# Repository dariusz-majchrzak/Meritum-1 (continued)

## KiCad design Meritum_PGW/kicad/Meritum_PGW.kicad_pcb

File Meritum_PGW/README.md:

# Meritum 1 - mainboard

This part of the project is the clone of the Meritum 1 mainboard.

## Files
This directory contains: 

* [BOM](bom) - Interactive HTML BOM
* [Gerber](gerber) - files (JLCPCB-compatible zip files)
* [IMG](img) - photos of the mainboard
* [KiCAD](kicad) - project design in KiCAD 10
* [Schematic](schematic) - Schematic in PDF format

## Assembling
WIP.

More to follow.

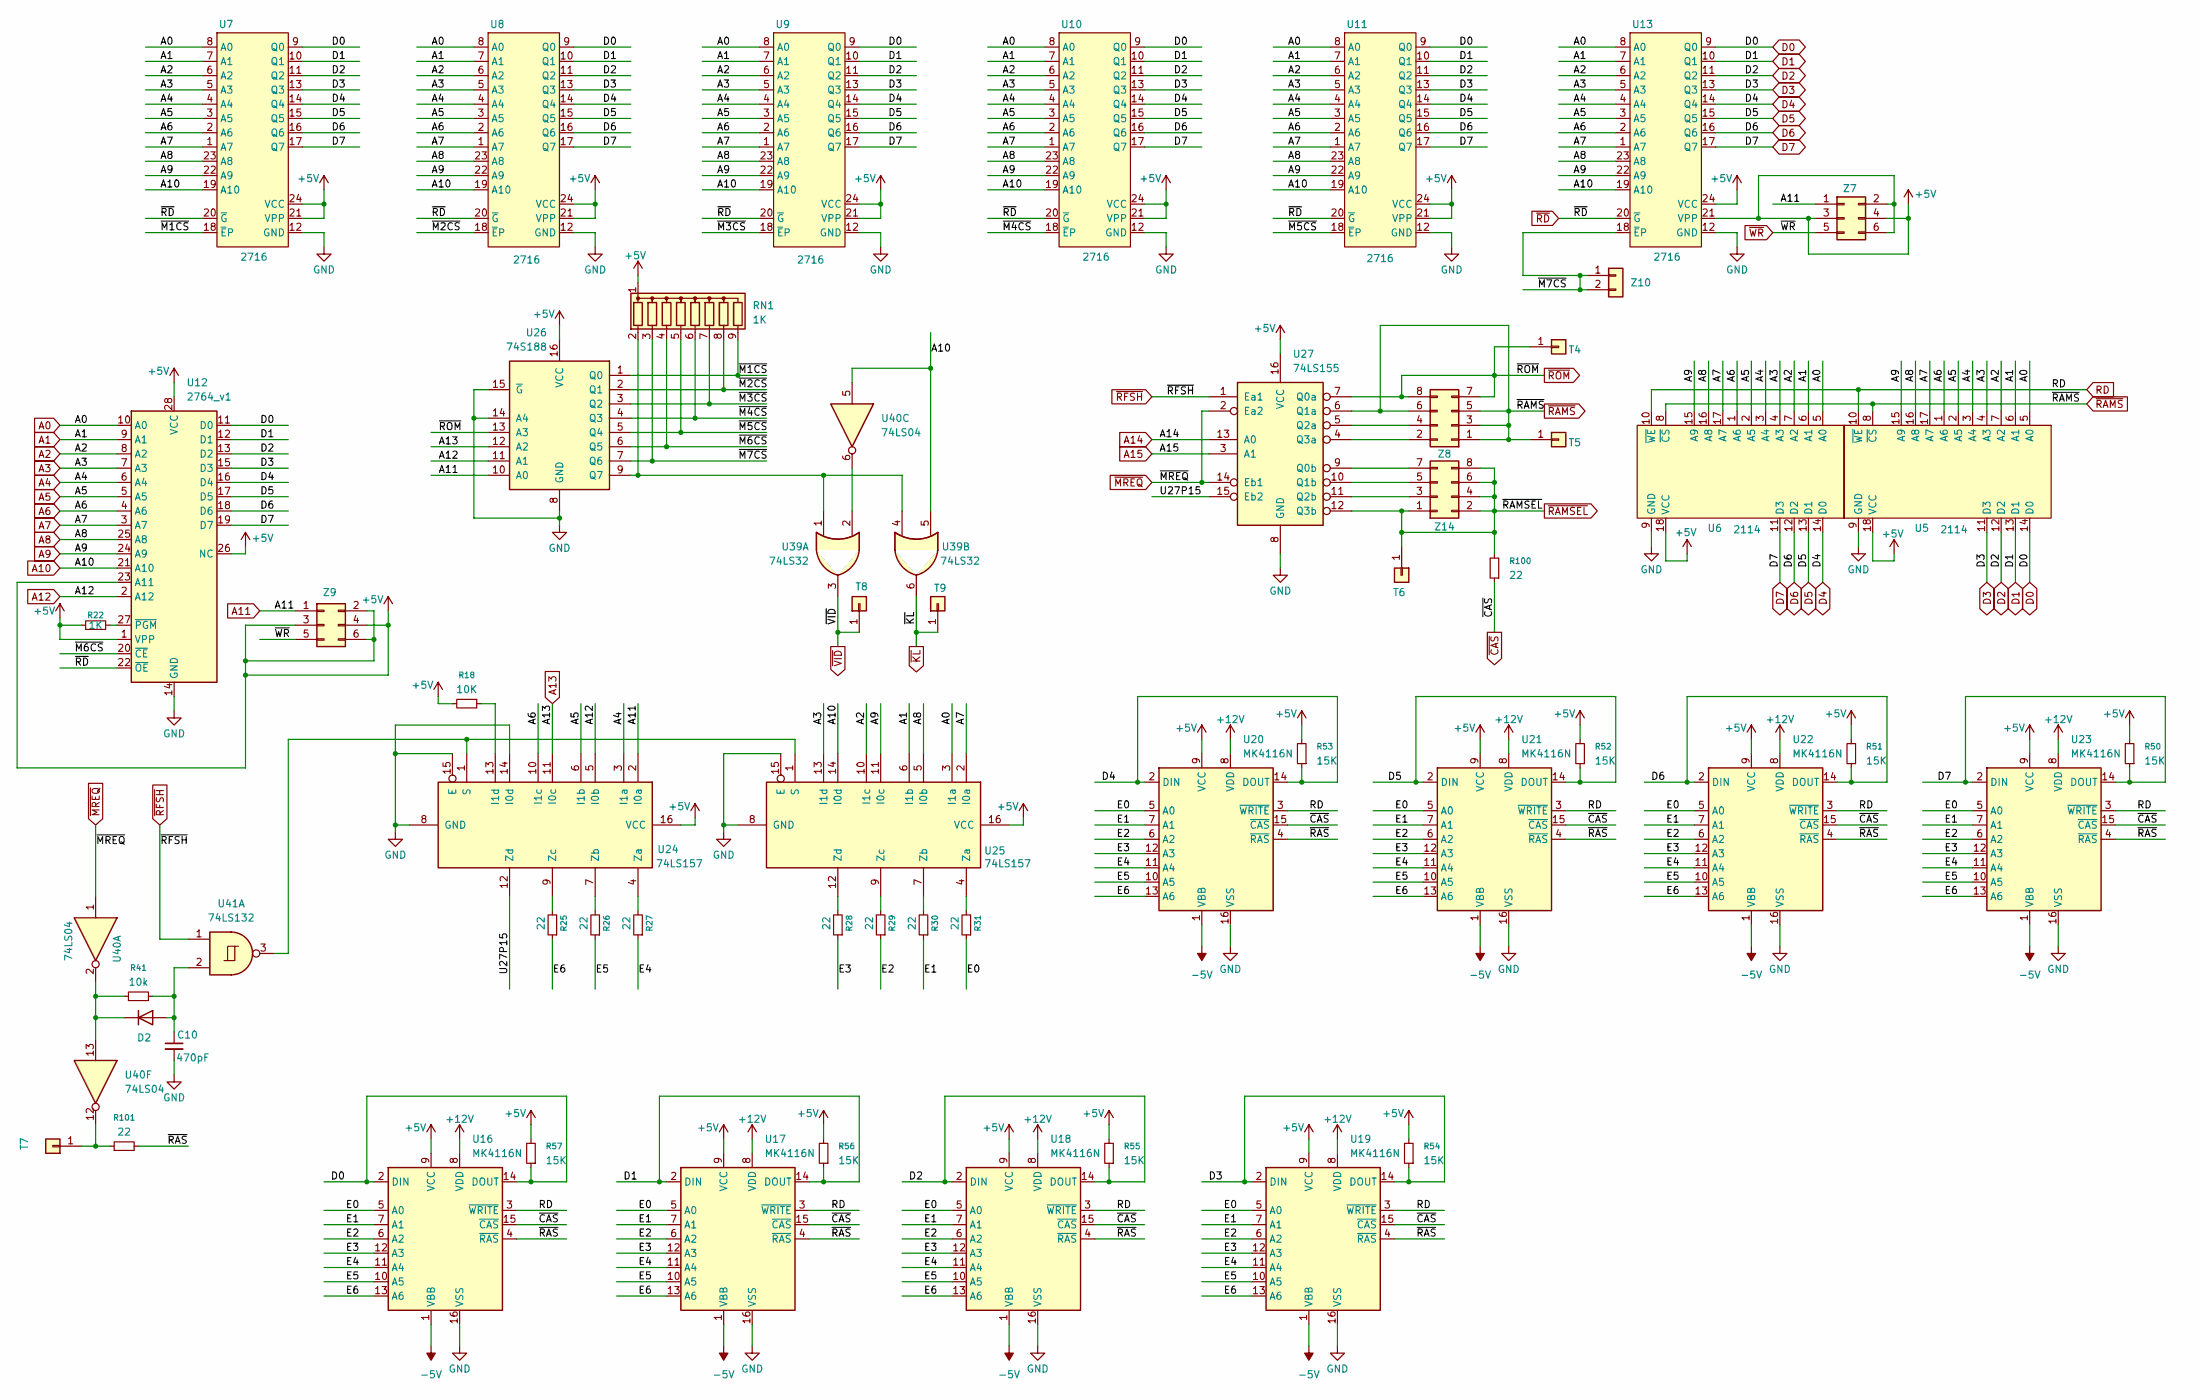
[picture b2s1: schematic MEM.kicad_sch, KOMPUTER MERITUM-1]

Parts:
C10: 470pF; c_100
D2: 1N4148; D_DO-35_SOD27_P10.16mm_Horizontal
R18: 10K; r_400
R22: 1K; R_Axial_DIN0207_L6.3mm_D2.5mm_P2.54mm_Vertical
R25, R26, R27, R28, R29, R30, R31, R100, R101: 22; r_400
R41: 10k; r_400
R50, R51, R52, R53, R54, R55, R56, R57: 15K; R_Axial_DIN0207_L6.3mm_D2.5mm_P2.54mm_Vertical
RN1: 1K; R_Array_SIP9
T4, T5, T6, T7, T8, T9: T18; pin
U5, U6: 2114; DIP-18_W7.62mm_Socket_LongPads
U7, U8, U9, U10, U11, U13: 2716; DIP-24_W15.24mm_LongPads
U12: 2764_v1; DIP-28_W15.24mm_LongPads
U16, U17, U18, U19, U20, U21, U22, U23: MK4116N; DIP-16_W7.62mm_LongPads
U24, U25: 74LS157; DIP-16_W7.62mm_LongPads
U26: 74S188; DIP-16_W7.62mm_LongPads
U27: 74LS155; DIP-16_W7.62mm_LongPads
U39: 74LS32; DIP-14_W7.62mm_LongPads
U40: 74LS04; DIP-14_W7.62mm_LongPads
U41: 74LS132; DIP-14_W7.62mm_LongPads
Z7: Z3; PinHeader_2x03_P2.54mm_Vertical
Z8, Z14: Conn_02x04_Odd_Even; PinHeader_2x04_P2.54mm_Vertical
Z9: Z4; PinHeader_2x03_P2.54mm_Vertical
Z10: Conn_01x02; PinHeader_1x02_P2.54mm_Vertical

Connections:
+5V: R18.2, R22.1, R50.2, R51.2, R52.2, R53.2, R54.2, R55.2, R56.2, R57.2, RN1.1 (common), U5.18 (VCC), U6.18 (VCC), U7.21 (VPP), U7.24 (VCC), U8.21 (VPP), U8.24 (VCC), U9.21 (VPP), U9.24 (VCC), U10.21 (VPP), U10.24 (VCC), U11.21 (VPP), U11.24 (VCC), U12.1 (VPP), U12.23 (A11), U12.26 (NC), U12.28 (VCC), U13.21 (VPP), U13.24 (VCC), U16.9 (VCC), U17.9 (VCC), U18.9 (VCC), U19.9 (VCC), U20.9 (VCC), U21.9 (VCC), U22.9 (VCC), U23.9 (VCC), U24.16 (VCC), U25.16 (VCC), U26.16 (VCC), U27.16 (VCC), Z7.2, Z7.3, Z7.4, Z7.6, Z9.2, Z9.3, Z9.4, Z9.6; also elsewhere on the board
+12V: U16.8 (VDD), U17.8 (VDD), U18.8 (VDD), U19.8 (VDD), U20.8 (VDD), U21.8 (VDD), U22.8 (VDD), U23.8 (VDD); also elsewhere on the board
-5V: U16.1 (VBB), U17.1 (VBB), U18.1 (VBB), U19.1 (VBB), U20.1 (VBB), U21.1 (VBB), U22.1 (VBB), U23.1 (VBB); also elsewhere on the board
/MEM/E0: R31.1, U16.5 (A0), U17.5 (A0), U18.5 (A0), U19.5 (A0), U20.5 (A0), U21.5 (A0), U22.5 (A0), U23.5 (A0)
/MEM/E1: R30.1, U16.7 (A1), U17.7 (A1), U18.7 (A1), U19.7 (A1), U20.7 (A1), U21.7 (A1), U22.7 (A1), U23.7 (A1)
/MEM/E2: R29.1, U16.6 (A2), U17.6 (A2), U18.6 (A2), U19.6 (A2), U20.6 (A2), U21.6 (A2), U22.6 (A2), U23.6 (A2)
/MEM/E3: R28.1, U16.12 (A3), U17.12 (A3), U18.12 (A3), U19.12 (A3), U20.12 (A3), U21.12 (A3), U22.12 (A3), U23.12 (A3)
/MEM/E4: R27.1, U16.11 (A4), U17.11 (A4), U18.11 (A4), U19.11 (A4), U20.11 (A4), U21.11 (A4), U22.11 (A4), U23.11 (A4)
/MEM/E5: R26.1, U16.10 (A5), U17.10 (A5), U18.10 (A5), U19.10 (A5), U20.10 (A5), U21.10 (A5), U22.10 (A5), U23.10 (A5)
/MEM/E6: R25.1, U16.13 (A6), U17.13 (A6), U18.13 (A6), U19.13 (A6), U20.13 (A6), U21.13 (A6), U22.13 (A6), U23.13 (A6)
/MEM/U27P15: U24.12 (Zd), U27.15 (Eb2)
/MEM/~M1CS: RN1.9 (R8), U7.18 (~EP), U26.1 (Q0)
/MEM/~M2CS: RN1.8 (R7), U8.18 (~EP), U26.2 (Q1)
/MEM/~M3CS: RN1.7 (R6), U9.18 (~EP), U26.3 (Q2)
/MEM/~M4CS: RN1.6 (R5), U10.18 (~EP), U26.4 (Q3)
/MEM/~M5CS: RN1.5 (R4), U11.18 (~EP), U26.5 (Q4)
/MEM/~M6CS: RN1.4 (R3), U12.20 (~CE), U26.6 (Q5)
/MEM/~M7CS: RN1.3 (R2), U13.18 (~EP), U26.7 (Q6), Z10.1, Z10.2
/MEM/~RAS: R101.2, U16.4 (~RAS), U17.4 (~RAS), U18.4 (~RAS), U19.4 (~RAS), U20.4 (~RAS), U21.4 (~RAS), U22.4 (~RAS), U23.4 (~RAS)
A0: U5.5 (A0), U6.5 (A0), U7.8 (A0), U8.8 (A0), U9.8 (A0), U10.8 (A0), U11.8 (A0), U12.10 (A0), U13.8 (A0), U25.3 (I1a); also elsewhere on the board
A1: U5.6 (A1), U6.6 (A1), U7.7 (A1), U8.7 (A1), U9.7 (A1), U10.7 (A1), U11.7 (A1), U12.9 (A1), U13.7 (A1), U25.6 (I1b); also elsewhere on the board
A2: U5.7 (A2), U6.7 (A2), U7.6 (A2), U8.6 (A2), U9.6 (A2), U10.6 (A2), U11.6 (A2), U12.8 (A2), U13.6 (A2), U25.10 (I1c); also elsewhere on the board
A3: U5.4 (A3), U6.4 (A3), U7.5 (A3), U8.5 (A3), U9.5 (A3), U10.5 (A3), U11.5 (A3), U12.7 (A3), U13.5 (A3), U25.13 (I1d); also elsewhere on the board
A4: U5.3 (A4), U6.3 (A4), U7.4 (A4), U8.4 (A4), U9.4 (A4), U10.4 (A4), U11.4 (A4), U12.6 (A4), U13.4 (A4), U24.3 (I1a); also elsewhere on the board
A5: U5.2 (A5), U6.2 (A5), U7.3 (A5), U8.3 (A5), U9.3 (A5), U10.3 (A5), U11.3 (A5), U12.5 (A5), U13.3 (A5), U24.6 (I1b); also elsewhere on the board
A6: U5.1 (A6), U6.1 (A6), U7.2 (A6), U8.2 (A6), U9.2 (A6), U10.2 (A6), U11.2 (A6), U12.4 (A6), U13.2 (A6), U24.10 (I1c); also elsewhere on the board
A7: U5.17 (A7), U6.17 (A7), U7.1 (A7), U8.1 (A7), U9.1 (A7), U10.1 (A7), U11.1 (A7), U12.3 (A7), U13.1 (A7), U25.2 (I0a); also elsewhere on the board
A8: U5.16 (A8), U6.16 (A8), U7.23 (A8), U8.23 (A8), U9.23 (A8), U10.23 (A8), U11.23 (A8), U12.25 (A8), U13.23 (A8), U25.5 (I0b); also elsewhere on the board
A9: U5.15 (A9), U6.15 (A9), U7.22 (A9), U8.22 (A9), U9.22 (A9), U10.22 (A9), U11.22 (A9), U12.24 (A9), U13.22 (A9), U25.11 (I0c); also elsewhere on the board
A10: U7.19 (A10), U8.19 (A10), U9.19 (A10), U10.19 (A10), U11.19 (A10), U12.21 (A10), U13.19 (A10), U25.14 (I0d), U39.5, U40.5; also elsewhere on the board
A11: U24.2 (I0a), U26.10 (A0), Z7.1, Z9.1; also elsewhere on the board
A12: U12.2 (A12), U24.5 (I0b), U26.11 (A1); also elsewhere on the board
A13: U24.11 (I0c), U26.12 (A2); also elsewhere on the board
A14: U27.13 (A0); also elsewhere on the board
A15: U27.3 (A1); also elsewhere on the board
BD0: R57.1, U5.14 (D0), U7.9 (Q0), U8.9 (Q0), U9.9 (Q0), U10.9 (Q0), U11.9 (Q0), U12.11 (D0), U13.9 (Q0), U16.2 (DIN), U16.14 (DOUT); also elsewhere on the board
D1: R56.1, U5.13 (D1), U7.10 (Q1), U8.10 (Q1), U9.10 (Q1), U10.10 (Q1), U11.10 (Q1), U12.12 (D1), U13.10 (Q1), U17.2 (DIN), U17.14 (DOUT); also elsewhere on the board
D2: R55.1, U5.12 (D2), U7.11 (Q2), U8.11 (Q2), U9.11 (Q2), U10.11 (Q2), U11.11 (Q2), U12.13 (D2), U13.11 (Q2), U18.2 (DIN), U18.14 (DOUT); also elsewhere on the board
D3: R54.1, U5.11 (D3), U7.13 (Q3), U8.13 (Q3), U9.13 (Q3), U10.13 (Q3), U11.13 (Q3), U12.15 (D3), U13.13 (Q3), U19.2 (DIN), U19.14 (DOUT); also elsewhere on the board
D4: R53.1, U6.14 (D0), U7.14 (Q4), U8.14 (Q4), U9.14 (Q4), U10.14 (Q4), U11.14 (Q4), U12.16 (D4), U13.14 (Q4), U20.2 (DIN), U20.14 (DOUT); also elsewhere on the board
D5: R52.1, U6.13 (D1), U7.15 (Q5), U8.15 (Q5), U9.15 (Q5), U10.15 (Q5), U11.15 (Q5), U12.17 (D5), U13.15 (Q5), U21.2 (DIN), U21.14 (DOUT); also elsewhere on the board
D6: R51.1, U6.12 (D2), U7.16 (Q6), U8.16 (Q6), U9.16 (Q6), U10.16 (Q6), U11.16 (Q6), U12.18 (D6), U13.16 (Q6), U22.2 (DIN), U22.14 (DOUT); also elsewhere on the board
D7: R50.1, U6.11 (D3), U7.17 (Q7), U8.17 (Q7), U9.17 (Q7), U10.17 (Q7), U11.17 (Q7), U12.19 (D7), U13.17 (Q7), U23.2 (DIN), U23.14 (DOUT); also elsewhere on the board
GND: C10.2, U5.9 (GND), U6.9 (GND), U7.12 (GND), U8.12 (GND), U9.12 (GND), U10.12 (GND), U11.12 (GND), U12.14 (GND), U13.12 (GND), U16.16 (VSS), U17.16 (VSS), U18.16 (VSS), U19.16 (VSS), U20.16 (VSS), U21.16 (VSS), U22.16 (VSS), U23.16 (VSS), U24.8 (GND), U24.14 (I0d), U24.15 (E), U25.8 (GND), U25.15 (E), U26.8 (GND), U26.14 (A4), U26.15 (~G), U27.8 (GND); also elsewhere on the board
unnamed: C10.1, D2.2 (A), R41.2, U41.2
unnamed: D2.1 (K), R41.1, U40.2, U40.13
unnamed: RN1.2 (R1), U26.9 (Q7), U39.1, U39.4
unnamed: R101.1, T7.1 (Pin_1_1), U40.12
unnamed: R22.2, U12.27 (~PGM)
unnamed: R18.1, U24.13 (I1d)
unnamed: U24.1 (S), U25.1 (S), U41.3
unnamed: R27.2, U24.4 (Za)
unnamed: R26.2, U24.7 (Zb)
unnamed: R25.2, U24.9 (Zc)
unnamed: R31.2, U25.4 (Za)
unnamed: R30.2, U25.7 (Zb)
unnamed: R29.2, U25.9 (Zc)
unnamed: R28.2, U25.12 (Zd)
unnamed: U27.9 (Q0b), Z14.7
unnamed: U27.10 (Q1b), Z14.5
unnamed: U27.5 (Q2a), Z8.4
unnamed: U27.11 (Q2b), Z14.3
unnamed: U27.4 (Q3a), Z8.2
unnamed: U39.2, U40.6
RD: U5.10 (~WE), U6.10 (~WE), U16.3 (~WRITE), U17.3 (~WRITE), U18.3 (~WRITE), U19.3 (~WRITE), U20.3 (~WRITE), U21.3 (~WRITE), U22.3 (~WRITE), U23.3 (~WRITE); also elsewhere on the board
~CAS: R100.1, U16.15 (~CAS), U17.15 (~CAS), U18.15 (~CAS), U19.15 (~CAS), U20.15 (~CAS), U21.15 (~CAS), U22.15 (~CAS), U23.15 (~CAS)
~KL: T9.1 (Pin_1_1), U39.6; also elsewhere on the board
~MREQ: U27.2 (Ea2), U27.14 (Eb1), U40.1; also elsewhere on the board
~RAMSEL: R100.2, T6.1 (Pin_1_1), U27.12 (Q3b), Z14.1, Z14.2, Z14.4, Z14.6, Z14.8; also elsewhere on the board
~RAMS: T5.1 (Pin_1_1), U5.8 (~CS), U6.8 (~CS), U27.6 (Q1a), Z8.1, Z8.3, Z8.5, Z8.6; also elsewhere on the board
~RD: U7.20 (~G), U8.20 (~G), U9.20 (~G), U10.20 (~G), U11.20 (~G), U12.22 (~OE), U13.20 (~G); also elsewhere on the board
~RFSH: U27.1 (Ea1), U41.1; also elsewhere on the board
~ROM: T4.1 (Pin_1_1), U26.13 (A3), U27.7 (Q0a), Z8.7, Z8.8; also elsewhere on the board
~VID: T8.1 (Pin_1_1), U39.3; also elsewhere on the board
~WR: Z7.5, Z9.5; also elsewhere on the board

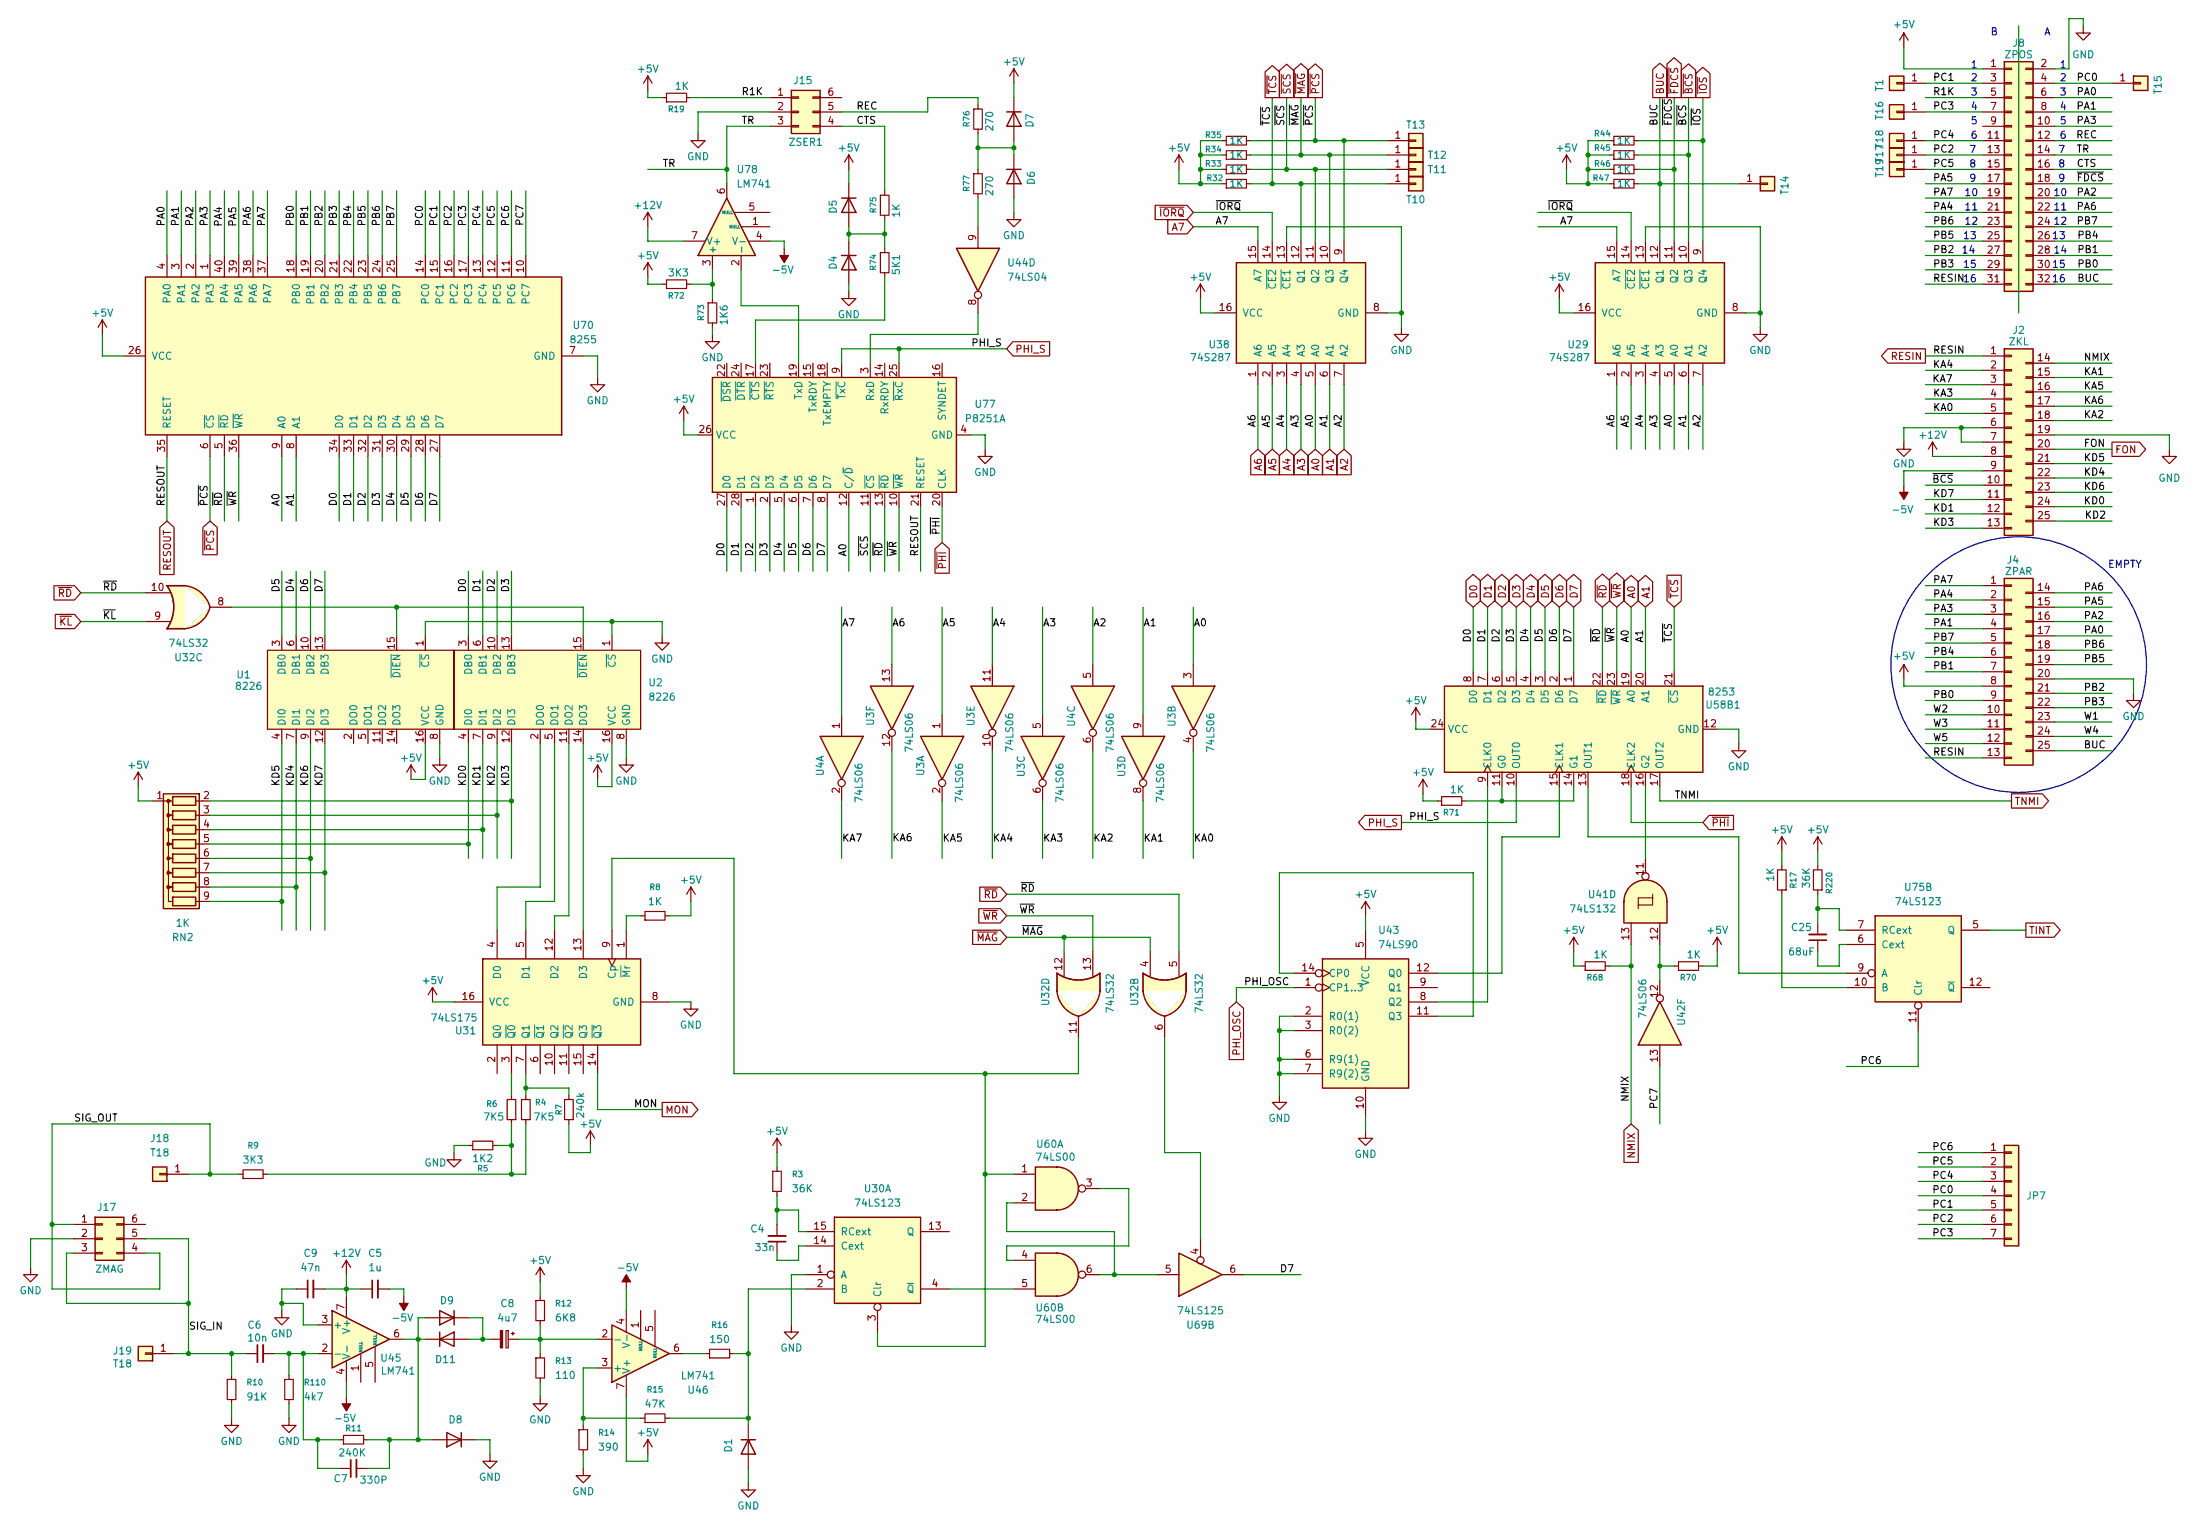
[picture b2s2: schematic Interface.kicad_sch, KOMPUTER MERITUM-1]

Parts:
C4: 33n; c_200
C5: 1u; c_200
C6: 10n; C_Rect_L4.0mm_W2.5mm_P2.50mm
C7: 330P; c_100
C8: 4u7; c_200
C9: 47n; c_200
C25: 68uF; CP_Radial_D5.0mm_P2.50mm
D1: 1N4148; D_DO-35_SOD27_P10.16mm_Horizontal
D4, D5: 1N4148WT; D_DO-35_SOD27_P2.54mm_Vertical_KathodeUp
D6, D7: 1N4148WT; D_DO-35_SOD27_P10.16mm_Horizontal
D8, D9, D11: 1N4148; D_DO-35_SOD27_P5.08mm_Vertical_AnodeUp
J2: ZKL; PinSocket_25_P2.54mm_Vertical
J4: ZPAR; PinSocket_25_P2.54mm_Vertical
J8: ZPOS; PinSocket_2x16_P2.54mm_Vertical_Meritum
J15: ZSER1; PinHeader_2x03_P2.54mm_Vertical
J17: ZMAG; PinHeader_2x03_P2.54mm_Vertical
J18, J19: T18; pin
JP7: Conn_01x07; PinHeader_1x07_P2.54mm_Vertical
R3, R220: 36K; r_400
R4, R6: 7K5; r_400
R5: 1K2; r_400
R7: 240k; r_400
R8, R17, R19, R32, R33, R34, R35, R44, R45, R46, R47, R68, R70, R75: 1K; r_400
R9, R72: 3K3; r_400
R10: 91K; R_Axial_DIN0207_L6.3mm_D2.5mm_P2.54mm_Vertical
R11: 240K; r_400
R12: 6K8; r_400
R13: 110; r_400
R14: 390; r_400
R15: 47K; r_400
R16: 150; r_400
R71: 1K; R_Axial_DIN0207_L6.3mm_D2.5mm_P2.54mm_Vertical
R73: 1K6; r_400
R74: 5K1; r_400
R76, R77: 270; r_400
R110: 4k7; R_Axial_DIN0207_L6.3mm_D2.5mm_P5.08mm_Vertical
RN2: 1K; R_Array_SIP9
T1, T10, T11, T12, T13, T14, T15, T16, T17, T18, T19: T18; pin
U1, U2: 8226; DIP-16_W7.62mm_LongPads
U3, U4, U42: 74LS06; DIP-14_W7.62mm_LongPads
U29, U38: 74S287; DIP-16_W7.62mm_LongPads
U30, U75: 74LS123; DIP-16_W7.62mm_LongPads
U31: 74LS175; DIP-16_W7.62mm_LongPads
U32: 74LS32; DIP-14_W7.62mm_LongPads
U41: 74LS132; DIP-14_W7.62mm_LongPads
U43: 74LS90; DIP-14_W7.62mm_LongPads
U44: 74LS04; DIP-14_W7.62mm_LongPads
U45, U46, U78: LM741; DIP-8_W7.62mm_LongPads
U58B1: 8253; DIP-24_W15.24mm_LongPads
U60: 74LS00; DIP-14_W7.62mm_LongPads
U69: 74LS125; DIP-14_W7.62mm_LongPads
U70: 8255; DIP-40_W15.24mm_LongPads
U77: P8251A; DIP-28_W15.24mm

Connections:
+5V: D5.1 (K), D7.1 (K), J4.8, J8.1, R3.1, R7.1, R8.2, R12.1, R17.2, R19.1, R32.1, R33.1, R34.1, R35.1, R44.1, R45.1, R46.1, R47.1, R68.1, R70.2, R71.1, R72.1, R220.2, RN2.1 (common), U1.16 (VCC), U2.16 (VCC), U29.16 (VCC), U31.16 (VCC), U38.16 (VCC), U43.5 (VCC), U46.7 (V+), U58B1.24 (VCC), U70.26 (VCC), U77.26 (VCC); also elsewhere on the board
+12V: C5.1, C9.2, J2.8, U45.7 (V+), U78.7 (V+); also elsewhere on the board
-5V: C5.2, J2.9, U45.4 (V-), U46.4 (V-), U78.4 (V-); also elsewhere on the board
/Interface/CTS: J8.16, J15.4, R75.1
/Interface/KA0: J2.5, U3.4
/Interface/KA1: J2.15, U3.8
/Interface/KA2: J2.18, U4.6
/Interface/KA3: J2.4, U3.6
/Interface/KA4: J2.2, U3.10
/Interface/KA5: J2.16, U3.2
/Interface/KA6: J2.17, U3.12
/Interface/KA7: J2.3, U4.2
/Interface/KD0: J2.24, RN2.5 (R4), U2.4 (DI0)
/Interface/KD1: J2.12, RN2.4 (R3), U2.7 (DI1)
/Interface/KD2: J2.25, RN2.3 (R2), U2.9 (DI2)
/Interface/KD3: J2.13, RN2.2 (R1), U2.12 (DI3)
/Interface/KD4: J2.22, RN2.8 (R7), U1.7 (DI1)
/Interface/KD5: J2.21, RN2.9 (R8), U1.4 (DI0)
/Interface/KD6: J2.23, RN2.6 (R5), U1.9 (DI2)
/Interface/KD7: J2.11, RN2.7 (R6), U1.12 (DI3)
/Interface/PA0: J4.17, J8.6, U70.4 (PA0)
/Interface/PA1: J4.4, J8.8, U70.3 (PA1)
/Interface/PA2: J4.16, J8.20, U70.2 (PA2)
/Interface/PA3: J4.3, J8.10, U70.1 (PA3)
/Interface/PA4: J4.2, J8.21, U70.40 (PA4)
/Interface/PA5: J4.15, J8.17, U70.39 (PA5)
/Interface/PA6: J4.14, J8.22, U70.38 (PA6)
/Interface/PA7: J4.1, J8.19, U70.37 (PA7)
/Interface/PB0: J4.9, J8.30, U70.18 (PB0)
/Interface/PB1: J4.7, J8.28, U70.19 (PB1)
/Interface/PB2: J4.21, J8.27, U70.20 (PB2)
/Interface/PB3: J4.22, J8.29, U70.21 (PB3)
/Interface/PB4: J4.6, J8.26, U70.22 (PB4)
/Interface/PB5: J4.19, J8.25, U70.23 (PB5)
/Interface/PB6: J4.18, J8.23, U70.24 (PB6)
/Interface/PB7: J4.5, J8.24, U70.25 (PB7)
/Interface/PC0: J8.4, JP7.4, T15.1 (Pin_1_1), U70.14 (PC0)
/Interface/PC1: J8.3, JP7.5, T1.1 (Pin_1_1), U70.15 (PC1)
/Interface/PC2: J8.13, JP7.6, T17.1 (Pin_1_1), U70.16 (PC2)
/Interface/PC3: J8.7, JP7.7, T16.1 (Pin_1_1), U70.17 (PC3)
/Interface/PC4: J8.11, JP7.3, T18.1 (Pin_1_1), U70.13 (PC4)
/Interface/PC5: J8.15, JP7.2, T19.1 (Pin_1_1), U70.12 (PC5)
/Interface/PC6: JP7.1, U70.11 (PC6), U75.11 (Clr)
/Interface/PC7: U42.13, U70.10 (PC7)
/Interface/R1K: J8.5, J15.1, R19.2
/Interface/REC: J8.12, J15.5, R76.1
/Interface/SIG_IN: C6.1, J17.3, J17.5, J19.1 (Pin_1_1), R10.1
/Interface/SIG_OUT: J17.1, J17.4, J18.1 (Pin_1_1), R9.1
/Interface/TR: J8.14, J15.3, U78.6
/Interface/W1: J4.23
/Interface/W2: J4.10
/Interface/W3: J4.11
/Interface/W4: J4.24
/Interface/W5: J4.12
A0: U3.3, U29.5 (A0), U38.5 (A0), U58B1.19 (A0), U70.9 (A0), U77.12 (C/~D); also elsewhere on the board
A1: U3.9, U29.6 (A1), U38.6 (A1), U58B1.20 (A1), U70.8 (A1); also elsewhere on the board
A2: U4.5, U29.7 (A2), U38.7 (A2); also elsewhere on the board
A3: U3.5, U29.4 (A3), U38.4 (A3); also elsewhere on the board
A4: U3.11, U29.3 (A4), U38.3 (A4); also elsewhere on the board
A5: U3.1, U29.2 (A5), U38.2 (A5); also elsewhere on the board
A6: U3.13, U29.1 (A6), U38.1 (A6); also elsewhere on the board
A7: U4.1, U29.15 (A7), U38.15 (A7); also elsewhere on the board
BD0: U2.3 (DB0), U58B1.8 (D0), U70.34 (D0), U77.27 (D0); also elsewhere on the board
BUC: J4.25, J8.32, R47.2, T14.1 (Pin_1_1), U29.12 (Q1)
D1: U2.6 (DB1), U58B1.7 (D1), U70.33 (D1), U77.28 (D1); also elsewhere on the board
D2: U2.10 (DB2), U58B1.6 (D2), U70.32 (D2), U77.1 (D2); also elsewhere on the board
D3: U2.13 (DB3), U58B1.5 (D3), U70.31 (D3), U77.2 (D3); also elsewhere on the board
D4: U1.6 (DB1), U58B1.4 (D4), U70.30 (D4), U77.5 (D4); also elsewhere on the board
D5: U1.3 (DB0), U58B1.3 (D5), U70.29 (D5), U77.6 (D5); also elsewhere on the board
D6: U1.10 (DB2), U58B1.2 (D6), U70.28 (D6), U77.7 (D6); also elsewhere on the board
D7: U1.13 (DB3), U58B1.1 (D7), U69.6, U70.27 (D7), U77.8 (D7); also elsewhere on the board
FON: J2.20; also elsewhere on the board
GND: C9.1, D1.2 (A), D4.2 (A), D6.2 (A), D8.1 (K), J2.6, J2.7, J2.19, J4.20, J8.2, J15.2, J17.2, R5.1, R10.2, R13.2, R14.2, R73.2, R110.2, U1.1 (~CS), U1.8 (GND), U2.1 (~CS), U2.8 (GND), U29.8 (GND), U29.13 (~CE1), U30.1 (A), U31.8 (GND), U38.8 (GND), U38.13 (~CE1), U43.2 (R0(1)), U43.3 (R0(2)), U43.6 (R9(1)), U43.7 (R9(2)), U43.10 (GND), U45.3 (+), U58B1.12 (GND), U70.7 (GND), U77.4 (GND); also elsewhere on the board
MON: U31.14 (~Q3); also elsewhere on the board
NMIX: J2.14, R68.2, U41.13
unnamed: D1.1 (K), R15.2, R16.2, U30.2 (B)
unnamed: D4.1 (K), D5.2 (A), R74.1, R75.2
unnamed: D6.1 (K), D7.2 (A), R76.2, R77.1
unnamed: C8.2, D9.1 (K), D11.2 (A)
unnamed: C7.2, D8.2 (A), D9.2 (A), D11.1 (K), R11.2, U45.6
unnamed: R4.1, R5.2, R6.1, R9.2
unnamed: R16.1, U46.6
unnamed: R70.1, U41.12, U42.12
unnamed: R77.2, U44.9
unnamed: U1.15 (~DIEN), U2.15 (~DIEN), U32.8
unnamed: U2.2 (DO0), U31.4 (D0)
unnamed: U2.5 (DO1), U31.5 (D1)
unnamed: U2.11 (DO2), U31.12 (D2)
unnamed: U2.14 (DO3), U31.13 (D3)
unnamed: C4.1, U30.14 (Cext)
unnamed: U30.3 (Clr), U31.9 (Cp), U32.11, U60.1
unnamed: C4.2, R3.2, U30.15 (RCext)
unnamed: U30.4 (~Q), U60.5
unnamed: R4.2, R7.2, U31.7 (Q1)
unnamed: R8.1, U31.1 (~Mr)
unnamed: R6.2, U31.3 (~Q0)
unnamed: U32.6, U69.4
unnamed: U43.11 (Q3), U43.14 (CP0)
unnamed: U43.12 (Q0), U58B1.15 (CLK1)
unnamed: U43.8 (Q2), U58B1.9 (CLK0)
unnamed: C6.2, C7.1, R11.1, R110.1, U45.2 (-)
unnamed: R14.1, R15.1, U46.3 (+)
unnamed: C8.1, R12.2, R13.1, U46.2 (-)
unnamed: R71.2, U58B1.11 (G0), U58B1.14 (G1)
unnamed: U41.11, U58B1.16 (G2)
unnamed: U58B1.13 (OUT1), U75.9 (A)
unnamed: U60.2, U60.6, U69.5
unnamed: U60.3, U60.4
unnamed: R17.1, U75.10 (B)
unnamed: C25.1, U75.6 (Cext)
unnamed: C25.2, R220.1, U75.7 (RCext)
unnamed: U44.8, U77.3 (RxD)
unnamed: U77.19 (TxD), U78.2 (-)
unnamed: R74.2, U77.17 (~CTS)
unnamed: R72.2, R73.1, U78.3 (+)
PHI_OSC: U43.1 (CP1..3); also elsewhere on the board
PHI_S: U58B1.10 (OUT0), U77.9 (~TxC), U77.25 (~RxC)
RESIN: J2.1, J4.13, J8.31; also elsewhere on the board
RESOUT: U70.35 (RESET), U77.21 (RESET); also elsewhere on the board
TINT: U75.5 (Q); also elsewhere on the board
TNMI: U58B1.17 (OUT2); also elsewhere on the board
~BCS: J2.10, R45.2, U29.10 (Q3)
~FDCS: J8.18, R46.2, U29.11 (Q2)
~IORQ: U29.14 (~CE2), U38.14 (~CE2); also elsewhere on the board
~IOS: R44.2, U29.9 (Q4); also elsewhere on the board
~KL: U32.9; also elsewhere on the board
~MAG: R34.2, T12.1 (Pin_1_1), U32.4, U32.12, U38.10 (Q3)
~PCS: R35.2, T13.1 (Pin_1_1), U38.9 (Q4), U70.6 (~CS)
~PHI: U58B1.18 (CLK2), U77.20 (CLK); also elsewhere on the board
~RD: U32.5, U32.10, U58B1.22 (~RD), U70.5 (~RD), U77.13 (~RD); also elsewhere on the board
~SCS: R33.2, T11.1 (Pin_1_1), U38.11 (Q2), U77.11 (~CS)
~TCS: R32.2, T10.1 (Pin_1_1), U38.12 (Q1), U58B1.21 (~CS)
~WR: U32.13, U58B1.23 (~WR), U70.36 (~WR), U77.10 (~WR); also elsewhere on the board

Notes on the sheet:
EMPTY

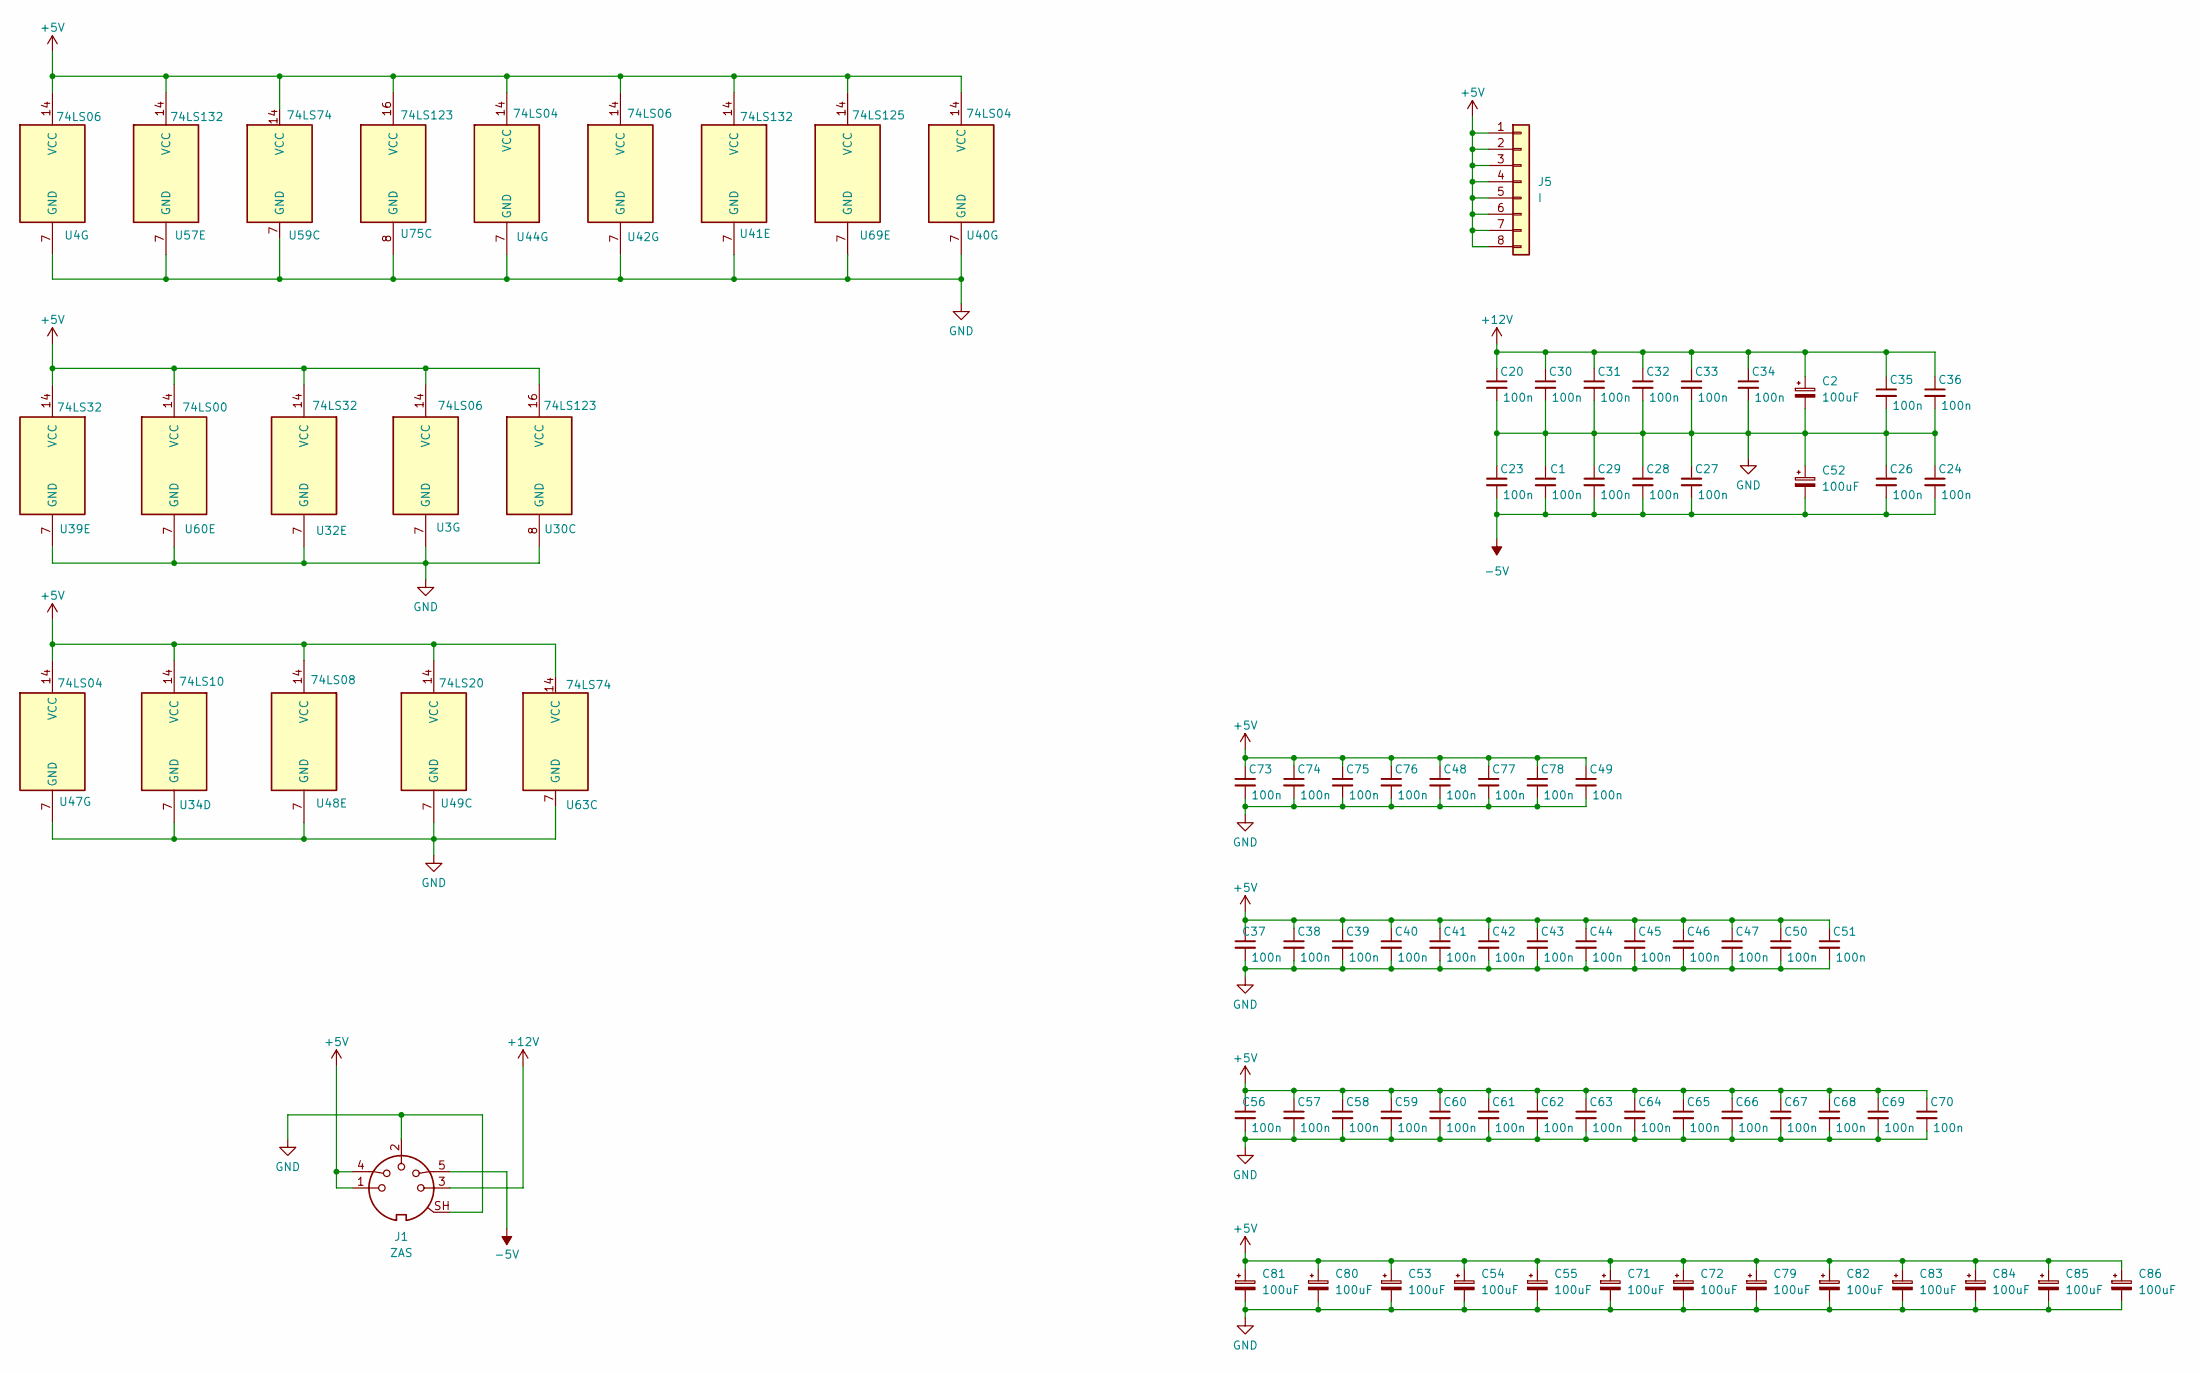
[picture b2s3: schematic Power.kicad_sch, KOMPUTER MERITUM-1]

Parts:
C1, C20, C23, C24, C26, C27, C28, C29, C30, C31, C32, C33, C34, C35, C36, C37, C38, C39, C40, C41, C42, C43, C44, C45, C46, C47, C50, C51, C56, C57, C58, C59, C60, C61, C62, C63, C64, C65, C66, C67, C68, C69, C70, C73, C74, C75, C76: 100n; c_200
C2, C52, C53, C54, C55, C71, C72, C79, C80, C81, C82, C83, C84, C85, C86: 100uF; CP_Radial_D5.0mm_P2.50mm
C48, C49, C77, C78: 100n; c_100
J1: ZAS; CUI_SDS-50J
J5: I; PinHeader_1x08_P2.54mm_Vertical
U3, U4, U42: 74LS06; DIP-14_W7.62mm_LongPads
U30, U75: 74LS123; DIP-16_W7.62mm_LongPads
U32, U39: 74LS32; DIP-14_W7.62mm_LongPads
U34: 74LS10; DIP-14_W7.62mm_LongPads
U40, U44, U47: 74LS04; DIP-14_W7.62mm_LongPads
U41, U57: 74LS132; DIP-14_W7.62mm_LongPads
U48: 74LS08; DIP-14_W7.62mm_LongPads
U49: 74LS20; DIP-14_W7.62mm_LongPads
U59, U63: 74LS74; DIP-14_W7.62mm_LongPads
U60: 74LS00; DIP-14_W7.62mm_LongPads
U69: 74LS125; DIP-14_W7.62mm_LongPads

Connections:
+5V: C37.1, C38.1, C39.1, C40.1, C41.1, C42.1, C43.1, C44.1, C45.1, C46.1, C47.1, C48.1, C49.1, C50.1, C51.1, C53.1, C54.1, C55.1, C56.1, C57.1, C58.1, C59.1, C60.1, C61.1, C62.1, C63.1, C64.1, C65.1, C66.1, C67.1, C68.1, C69.1, C70.1, C71.1, C72.1, C73.1, C74.1, C75.1, C76.1, C77.1, C78.1, C79.1, C80.1, C81.1, C82.1, C83.1, C84.1, C85.1, C86.1, J1.1, J1.4, J5.1, J5.2, J5.3, J5.4, J5.5, J5.6, J5.7, J5.8, U3.14 (VCC), U4.14 (VCC), U30.16 (VCC), U32.14 (VCC), U34.14 (VCC), U39.14 (VCC), U40.14 (VCC), U41.14 (VCC), U42.14 (VCC), U44.14 (VCC), U47.14 (VCC), U48.14 (VCC), U49.14 (VCC), U57.14 (VCC), U59.14 (VCC), U60.14 (VCC), U63.14 (VCC), U69.14 (VCC), U75.16 (VCC); also elsewhere on the board
+12V: C2.1, C20.1, C30.1, C31.1, C32.1, C33.1, C34.1, C35.1, C36.1, J1.3; also elsewhere on the board
-5V: C1.2, C23.2, C24.2, C26.2, C27.2, C28.2, C29.2, C52.2, J1.5; also elsewhere on the board
GND: C1.1, C2.2, C20.2, C23.1, C24.1, C26.1, C27.1, C28.1, C29.1, C30.2, C31.2, C32.2, C33.2, C34.2, C35.2, C36.2, C37.2, C38.2, C39.2, C40.2, C41.2, C42.2, C43.2, C44.2, C45.2, C46.2, C47.2, C48.2, C49.2, C50.2, C51.2, C52.1, C53.2, C54.2, C55.2, C56.2, C57.2, C58.2, C59.2, C60.2, C61.2, C62.2, C63.2, C64.2, C65.2, C66.2, C67.2, C68.2, C69.2, C70.2, C71.2, C72.2, C73.2, C74.2, C75.2, C76.2, C77.2, C78.2, C79.2, C80.2, C81.2, C82.2, C83.2, C84.2, C85.2, C86.2, J1.2, J1.SH, U3.7 (GND), U4.7 (GND), U30.8 (GND), U32.7 (GND), U34.7 (GND), U39.7 (GND), U40.7 (GND), U41.7 (GND), U42.7 (GND), U44.7 (GND), U47.7 (GND), U48.7 (GND), U49.7 (GND), U57.7 (GND), U59.7 (GND), U60.7 (GND), U63.7 (GND), U69.7 (GND), U75.8 (GND); also elsewhere on the board
